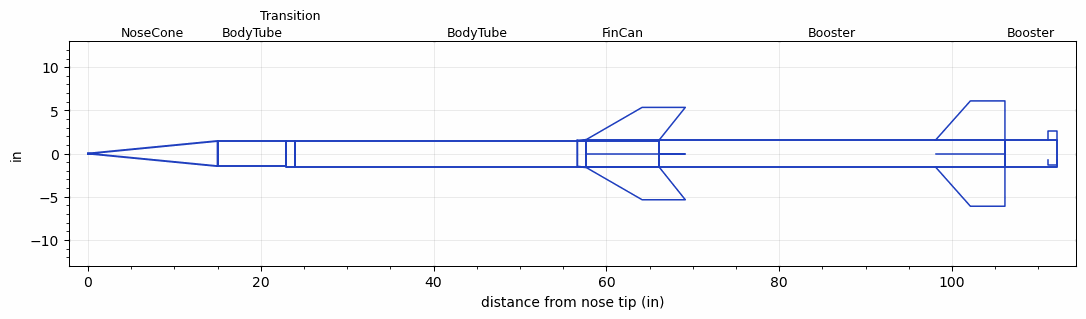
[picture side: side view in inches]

<RASAeroDocument>
 <FileVersion>2</FileVersion>
 <RocketDesign>
  <NoseCone>
   <Length>15</Length>
   <Diameter>2.91</Diameter>
   <Shape>Conical</Shape>
   <BluntRadius>0.065</BluntRadius>
   <Location>0</Location>
  </NoseCone>
  <BodyTube>
   <Length>7.94</Length>
   <Diameter>2.91</Diameter>
   <Location>15</Location>
   <Protuberance>
    <StreamlinedNoBaseDrag>0</StreamlinedNoBaseDrag>
    <StreamlinedWithBaseDrag>0.65</StreamlinedWithBaseDrag>
    <InclinedPlate1Angle>0</InclinedPlate1Angle>
    <InclinedPlate1FrontalArea>0</InclinedPlate1FrontalArea>
    <InclinedPlate2Angle>0</InclinedPlate2Angle>
    <InclinedPlate2FrontalArea>0</InclinedPlate2FrontalArea>
   </Protuberance>
  </BodyTube>
  <Transition>
   <Length>1</Length>
   <Diameter>3</Diameter>
   <Location>22.94</Location>
   <RearDiameter>3</RearDiameter>
  </Transition>
  <BodyTube>
   <Length>42.195</Length>
   <Diameter>3</Diameter>
   <Location>23.94</Location>
  </BodyTube>
  <FinCan>
   <Length>8.5</Length>
   <Diameter>3.19</Diameter>
   <InsideDiameter>3</InsideDiameter>
   <Location>66.135</Location>
   <ShoulderLength>1</ShoulderLength>
   <Offset>-8.5</Offset>
   <Fin>
    <Count>4</Count>
    <Chord>8.5</Chord>
    <Span>3.75</Span>
    <SweepDistance>6.5</SweepDistance>
    <TipChord>5</TipChord>
    <Thickness>0.15</Thickness>
    <LERadius>0.01</LERadius>
    <Location>8.5</Location>
    <AirfoilSection>Hexagonal</AirfoilSection>
    <FX1>0.75</FX1>
    <FX3>0.75</FX3>
   </Fin>
  </FinCan>
  <Booster>
   <Length>40</Length>
   <Diameter>3.19</Diameter>
   <InsideDiameter>3.19</InsideDiameter>
   <LaunchShoeArea>0.4</LaunchShoeArea>
   <Location>66.135</Location>
   <ShoulderLength>0</ShoulderLength>
   <Fin>
    <Count>4</Count>
    <Chord>8</Chord>
    <Span>4.5</Span>
    <SweepDistance>4</SweepDistance>
    <TipChord>4</TipChord>
    <Thickness>0.1875</Thickness>
    <LERadius>0.01</LERadius>
    <Location>8</Location>
    <AirfoilSection>Hexagonal</AirfoilSection>
    <FX1>0.5</FX1>
    <FX3>0.5</FX3>
   </Fin>
  </Booster>
  <Booster>
   <Length>6</Length>
   <Diameter>3.19</Diameter>
   <InsideDiameter>3.19</InsideDiameter>
   <Location>106.135</Location>
   <ShoulderLength>0</ShoulderLength>
   <Fin>
    <Count>3</Count>
    <Chord>1</Chord>
    <Span>1</Span>
    <SweepDistance>0</SweepDistance>
    <TipChord>1</TipChord>
    <Thickness>0.1</Thickness>
    <Location>1</Location>
    <AirfoilSection>Square</AirfoilSection>
   </Fin>
  </Booster>
  <Surface>Rough Camouflage Paint</Surface>
  <ModifiedBarrowman>True</ModifiedBarrowman>
  <Turbulence>True</Turbulence>
  <UseBooster1>False</UseBooster1>
  <UseBooster2>False</UseBooster2>
 </RocketDesign>
 <LaunchSite>
  <Altitude>2000</Altitude>
  <Pressure>0</Pressure>
  <RodAngle>1</RodAngle>
  <RodLength>20</RodLength>
  <Temperature>80</Temperature>
  <WindSpeed>5</WindSpeed>
 </LaunchSite>
 <Recovery>
  <Altitude1>1000</Altitude1>
  <Altitude2>1000</Altitude2>
  <DeviceType1>None</DeviceType1>
  <DeviceType2>None</DeviceType2>
  <Event1>False</Event1>
  <Event2>False</Event2>
  <Size1>1</Size1>
  <Size2>1</Size2>
  <EventType1>None</EventType1>
  <EventType2>None</EventType2>
  <CD1>1.33</CD1>
  <CD2>1.33</CD2>
 </Recovery>
 <SimulationList>
  <Simulation>
   <SustainerEngine>N3051  (TsKrush)</SustainerEngine>
   <SustainerLaunchWt>22.67</SustainerLaunchWt>
   <SustainerNozzleDiameter>2.5</SustainerNozzleDiameter>
   <SustainerCG>43</SustainerCG>
   <SustainerIgnitionDelay>8</SustainerIgnitionDelay>
   <Booster1Engine>M3140  (TsKrush)</Booster1Engine>
   <Booster1LaunchWt>38.84</Booster1LaunchWt>
   <Booster1SeparationDelay>0</Booster1SeparationDelay>
   <Booster1IgnitionDelay>5</Booster1IgnitionDelay>
   <Booster1CG>58.5</Booster1CG>
   <Booster1NozzleDiameter>2.75</Booster1NozzleDiameter>
   <IncludeBooster1>True</IncludeBooster1>
   <Booster2Engine>M3140  (TsKrush)</Booster2Engine>
   <Booster2Delay>0</Booster2Delay>
   <IncludeBooster2>False</IncludeBooster2>
   <TimetoApogee>82.38866</TimetoApogee>
   <MaxAltitude>108434.8</MaxAltitude>
   <MaxVelocity>4481.245</MaxVelocity>
  </Simulation>
 </SimulationList>
</RASAeroDocument>
